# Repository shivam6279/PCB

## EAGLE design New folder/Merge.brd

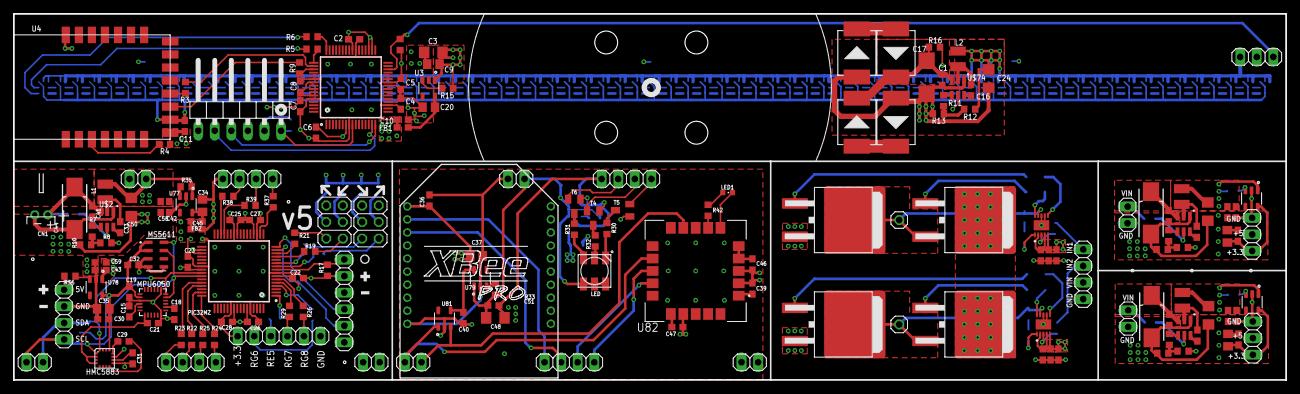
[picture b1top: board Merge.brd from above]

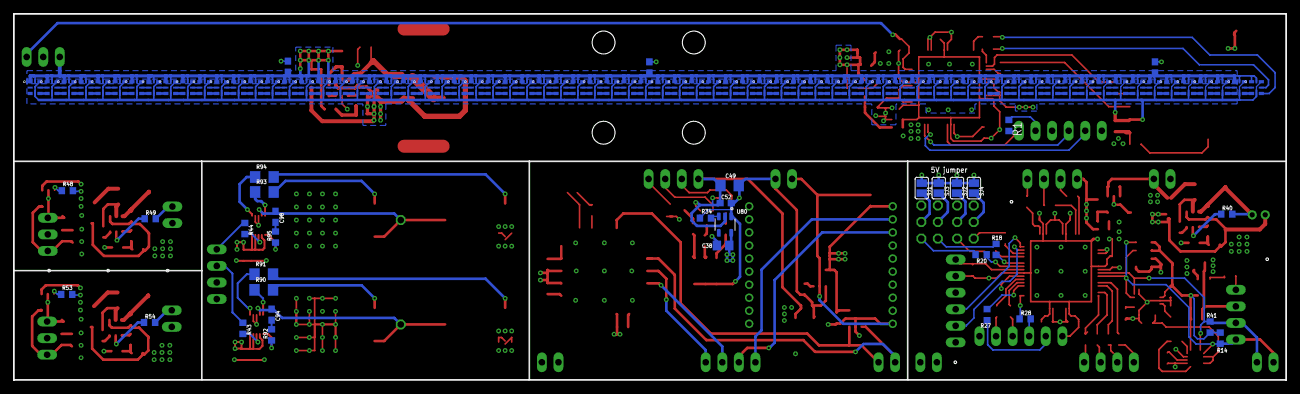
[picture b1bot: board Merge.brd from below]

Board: 4 copper layers, 195.0 x 56.1 mm, 281 parts (107 on the bottom side), 289 nets.

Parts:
C1, C2, C4, C5, C6, C7, C8, C10, C11, C12, C13, C14, C15, C16, C21, C22, C23, C25, C26, C27, C28, C30, C32, C33, C36, C39, C40, C41, C42, C43, C45, C46, C47, C51, C52, C53, C55, C56, C58, C59, C60, C62, C63, C65, C66, C68, C70: 0.1uF; C0603
C3, C24, C48, C49, C50, C61, C69: 10uF; C1206
C9: C0805
C17: C/6032-28R
C18: 2.2nF; C0603
C19: 10nF; C0603
C20, C34, C35, C37, C38, C54, C64: 1uF; C0805
C29: 0.22uF; C0603
C31: 4.7uF; C0603
C44, C57, C67: 085CS_1AR
C91, C92, C93, C94, C95, C96, C97, C98: C0603
CN1: JST-PH-2-THM-RA
D2, D3, D4, D5: SMD-DIODE-SCHOTTKY-40V-3A(DO-214AB); DO-214AB
E$1: 1X04
E$2, E$4: 1X02
E$3, E$5: 1X03
FB1, FB2: 30Ω/1.8A; 0603
HMC5883: HMC5883L; LPCC-16
JP1: 1X06/90
JP2: 1X03
JP3, JP10, JP12, JP13, JP14, JP15: 1X02
JP4, JP5: 2X03
JP6, JP7, JP8, JP9, JP11: 1X04
JP16, JP17: 1X06
JP29, JP30: 1X01
L1, L2, L3, L4: 4.7uH; L2825P
LED: RGBLED5050
LED1: CHIPLED_0603
MPU6050: MPU-6050; QFN50P400X400X95-24N
MS5611: MS561101BA03-50; SON125P500X300X100-8N
PIC32MZ: PIC32MZ2048EFH064-I/PT; QFP50P1200X1200X120-64N
R1, R2, R3, R4, R5, R6, R9, R43, R44, R92, R95: R0603
R7, R11, R15, R45, R50: 75k; R0603
R8, R12, R46, R51: 41k; R0603
R10, R13, R47, R52: 7.6k; R0603
R14, R41: 4.7k; R0603
R16: 20k; R0603
R17, R42: 1k; R0603
R18, R19, R20, R21, R22, R23, R24, R25, R26, R27, R28, R29, R37, R38, R39: 33; R0603
R30, R31: 330; R0603
R32: 220; R0603
R33, R34, R35, R36, R40, R48, R49, R53, R54: 10k; R0603
R90, R91, R93, R94: R1206
SJ1, SJ2, SJ3, SJ4: SJ
T1, T2, T3, T7: D2PAK_TO263
T4, T5, T6: SOT23-EBC
U1: PIC32MZ2048EFH064-I/PT; QFP50P1200X1200X120-64N
U2, U5, U6, U7, U8, U9, U10, U11, U12, U13, U14, U15, U16, U17, U18, U19, U20, U21, U22, U23, U24, U25, U26, U27, U28, U29, U30, U31, U32, U33, U34, U35, U36, U37, U38, U39, U40, U41, U42, U43, U44, U45, U46, U47, U48, U49, U50, U51, U52, U53, U54, U55, U56, U57, U58, U59, U60, U61, U62, U63, U64, U65, U66, U67, U68, U69, U70, U71, U72, U73, U74, U75, U76: 3341; LED_3341
U3, U77, U78, U79, U80, U83, U84: TLV75533PDBVR; SOT95P280X145-5N
U4: EMB1061
U81: CAT24C02; SOT95P280X145-5N
U82: SAM-M8Q; XCVR_SAM-M8Q
U90, U91: CHL8510CRT; 10-VFDFN
U$1, U$2, U$3, U$74: AP65211A; SOT95P280X140-6N
XB2: XBEE-PRO

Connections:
+3V1: C22.1, C23.1, C25.1, C26.1, C27.1, C28.1, C45.1, FB2.2, JP16.6, JP17.2, PIC32MZ.8, PIC32MZ.19, PIC32MZ.26, PIC32MZ.39, PIC32MZ.54, PIC32MZ.60, R17.2
+3V3: C2.1, C4.1, C5.1, C6.1, C7.1, C8.1, C10.1, C11.1, FB1.2, JP1.5, R1.1, R2.1, R4.1, U1.8, U1.19, U1.26, U1.39, U1.54, U1.60, U4.P$8
+5V: C3.1, C9.1, C12.1, C13.1, C14.1, C24.1, JP2.1, L2.1, R12.2, R15.1, U2.1, U2.8, U3.1, U5.1, U5.8, U6.1, U6.8, U7.1, U7.8, U8.1, U8.8, U9.1, U9.8, U10.1, U10.8, U11.1, U11.8, U12.1, U12.8, U13.1, U13.8, U14.1, U14.8, U15.1, U15.8, U16.1, U16.8, U17.1, U17.8, U18.1, U18.8, U19.1, U19.8, U20.1, U20.8, U21.1, U21.8, U22.1, U22.8, U23.1, U23.8, U24.1, U24.8, U25.1, U25.8, U26.1, U26.8, U27.1, U27.8, U28.1, U28.8, U29.1, U29.8, U30.1, U30.8, U31.1, U31.8, U32.1, U32.8, U33.1, U33.8, U34.1, U34.8, U35.1, U35.8, U36.1, U36.8, U37.1, U37.8, U38.1, U38.8, U39.1, U39.8, U40.1, U40.8, U41.1, U41.8, U42.1, U42.8, U43.1, U43.8, U44.1, U44.8, U45.1, U45.8, U46.1, U46.8, U47.1, U47.8, U48.1, U48.8, U49.1, U49.8, U50.1, U50.8, U51.1, U51.8, U52.1, U52.8, U53.1, U53.8, U54.1, U54.8, U55.1, U55.8, U56.1, U56.8, U57.1, U57.8, U58.1, U58.8, U59.1, U59.8, U60.1, U60.8, U61.1, U61.8, U62.1, U62.8, U63.1, U63.8, U64.1, U64.8, U65.1, U65.8, U66.1, U66.8, U67.1, U67.8, U68.1, U68.8, U69.1, U69.8, U70.1, U70.8, U71.1, U71.8, U72.1, U72.8, U73.1, U73.8, U74.1, U74.8, U75.1, U75.8, U76.1, U76.8
+5V1: C42.1, C43.1, C50.1, C58.1, C59.1, JP7.4, JP10.1, L1.1, R8.2, R35.2, R36.2, SJ1.2, SJ2.2, SJ3.2, SJ4.2, U77.1, U78.1
+5V2: C56.1, C61.1, C62.1, E$3.2, L3.1, R46.2, R48.2, U83.1
+5V3: C66.1, C69.1, C70.1, E$5.2, L4.1, R51.2, R53.2, U84.1
+5V/1: C48.1, C49.1, C51.1, C52.1, JP13.1, LED.1, LED.2, LED.3, R33.2, R34.2, U79.1, U80.1
+12V: C41.1, C44.+, CN1.1, R40.2, U$2.3
+12V1: C55.1, C57.+, E$2.2, R49.2, U$1.3
+12V2: C91.1, C92.1, C93.1, C95.1, C96.1, C97.1, E$1.2, T1.2, T3.2, U90.2, U90.4, U90.5, U91.2, U91.4, U91.5
+12V3: C65.1, C67.+, E$4.2, R54.2, U$3.3
+15V: C1.1, C17.+, D2.2, D3.2, R16.2, U$74.3
BLE_RX: R3.2, U4.P$11
BLE_TX: R9.2, U4.P$10
CKI_1: R5.2, U2.5
DGND: C36.2, C37.2, C38.2, C39.2, C40.2, C46.2, C47.2, C48.2, C49.2, C51.2, C52.2, JP8.4, JP13.2, JP14.1, JP14.2, LED1.C, T4.E, T5.E, T6.E, U79.2, U80.2, U81.2, U82.1, U82.4, U82.5, U82.6, U82.10, U82.11, U82.15, U82.16, U82.20, XB2.10
ESC_1: JP5.1, R20.2
ESC_2: JP5.2, R18.2
ESC_3: JP4.1, R19.2
ESC_4: JP4.2, R21.2
GATE_H1: R90.2, T1.1
GATE_H2: R93.2, T3.1
GATE_L1: R91.2, T7.1
GATE_L2: R94.2, T2.1
GND1: C1.2, C2.2, C3.2, C4.2, C5.2, C6.2, C7.2, C8.2, C9.2, C10.2, C11.2, C12.2, C13.2, C14.2, C15.2, C17.-, C18.2, C19.2, C20.2, C21.2, C22.2, C23.2, C24.2, C25.2, C26.2, C27.2, C28.2, C30.2, C31.2, C32.2, C34.2, C35.2, C41.2, C42.2, C43.2, C44.-, C45.2, C50.2, C58.2, C59.2, CN1.2, D4.1, D5.1, HMC5883.9, HMC5883.11, JP1.4, JP2.2, JP4.5, JP4.6, JP5.5, JP5.6, JP7.3, JP9.4, JP10.2, JP15.1, JP15.2, JP16.1, JP17.3, MPU6050.1, MPU6050.9, MPU6050.18, MS5611.3, MS5611.4, MS5611.5, PIC32MZ.7, PIC32MZ.20, PIC32MZ.25, PIC32MZ.34, PIC32MZ.35, PIC32MZ.40, PIC32MZ.55, PIC32MZ.59, R10.1, R13.1, U1.7, U1.20, U1.25, U1.34, U1.35, U1.40, U1.55, U1.59, U2.6, U2.7, U3.2, U4.P$9, U4.P$22, U5.6, U5.7, U6.6, U6.7, U7.6, U7.7, U8.6, U8.7, U9.6, U9.7, U10.6, U10.7, U11.6, U11.7, U12.6, U12.7, U13.6, U13.7, U14.6, U14.7, U15.6, U15.7, U16.6, U16.7, U17.6, U17.7, U18.6, U18.7, U19.6, U19.7, U20.6, U20.7, U21.6, U21.7, U22.6, U22.7, U23.6, U23.7, U24.6, U24.7, U25.6, U25.7, U26.6, U26.7, U27.6, U27.7, U28.6, U28.7, U29.6, U29.7, U30.6, U30.7, U31.6, U31.7, U32.6, U32.7, U33.6, U33.7, U34.6, U34.7, U35.6, U35.7, U36.6, U36.7, U37.6, U37.7, U38.6, U38.7, U39.6, U39.7, U40.6, U40.7, U41.6, U41.7, U42.6, U42.7, U43.6, U43.7, U44.6, U44.7, U45.6, U45.7, U46.6, U46.7, U47.6, U47.7, U48.6, U48.7, U49.6, U49.7, U50.6, U50.7, U51.6, U51.7, U52.6, U52.7, U53.6, U53.7, U54.6, U54.7, U55.6, U55.7, U56.6, U56.7, U57.6, U57.7, U58.6, U58.7, U59.6, U59.7, U60.6, U60.7, U61.6, U61.7, U62.6, U62.7, U63.6, U63.7, U64.6, U64.7, U65.6, U65.7, U66.6, U66.7, U67.6, U67.7, U68.6, U68.7, U69.6, U69.7, U70.6, U70.7, U71.6, U71.7, U72.6, U72.7, U73.6, U73.7, U74.6, U74.7, U75.6, U75.7, U76.6, U76.7, U77.2, U78.2, U$2.1, U$74.1
GND2: C54.2, C55.2, C56.2, C57.-, C60.1, C61.2, C62.2, E$2.1, E$3.1, R47.1, U83.2, U$1.1
GND3: C91.2, C92.2, C93.2, C95.2, C96.2, C97.2, E$1.1, T2.3, T7.3, U90.7, U90.8, U90.11, U91.7, U91.8, U91.11
GND4: C64.2, C65.2, C66.2, C67.-, C68.1, C69.2, C70.2, E$4.1, E$5.1, R52.1, U84.2, U$3.1
GPIO1: JP16.5, R27.2
GPIO2: JP16.4, R28.2
GPIO3: JP16.3, R29.2
GPIO4: JP16.2, R26.2
GPS_RX: JP11.1, R23.1
GPS_RX_J: JP6.3, U82.14
GPS_TX: JP11.2, R22.1
GPS_TX_J: JP6.4, U82.13
H_OUT1: C94.1, JP29.1, T1.3, T7.2, U90.9
H_OUT2: C98.1, JP30.1, T2.2, T3.3, U91.9
LED_BLUE: JP9.1, R37.2
LED_BLUE1: JP8.1, T5.B
LED_GREEN: JP9.3, R38.2
LED_GREEN1: JP8.2, T4.B
LED_RED: JP9.2, R39.2
MCLR: JP17.1, PIC32MZ.9, R17.1
unnamed: D2.1, D5.2
unnamed: D3.1, D4.2
unnamed: R15.2, U3.3
unnamed: R9.1, U1.51
unnamed: R4.2, U4.P$3
unnamed: R16.1, U$74.5
unnamed: U5.2, U6.5
unnamed: U5.3, U6.4
unnamed: U2.2, U5.5
unnamed: U2.3, U5.4
unnamed: U6.2, U7.5
unnamed: JP1.3, U1.16
unnamed: JP1.2, U1.15
unnamed: JP1.6, R1.2, U1.9
unnamed: U26.2, U27.5
unnamed: U6.3, U7.4
unnamed: U7.2, U8.5
unnamed: U7.3, U8.4
unnamed: R3.1, U1.50
unnamed: U8.2, U9.5
unnamed: R6.1, U1.48
unnamed: U8.3, U9.4
unnamed: U9.2, U10.5
unnamed: U9.3, U10.4
unnamed: U10.2, U11.5
unnamed: U10.3, U11.4
unnamed: U11.2, U12.5
unnamed: U11.3, U12.4
unnamed: U12.2, U13.5
unnamed: U12.3, U13.4
unnamed: U13.2, U14.5
unnamed: U13.3, U14.4
unnamed: U14.2, U15.5
unnamed: U14.3, U15.4
unnamed: U15.2, U17.5
unnamed: U15.3, U17.4
unnamed: U16.5, U17.2
unnamed: U16.4, U17.3
unnamed: U18.2, U19.5
unnamed: U18.3, U19.4
unnamed: U16.2, U18.5
unnamed: R5.1, U1.49
unnamed: U16.3, U18.4
unnamed: U19.2, U20.5
unnamed: U19.3, U20.4
unnamed: U20.2, U21.5
unnamed: JP2.3, R2.2, U1.30
unnamed: U20.3, U21.4
unnamed: U21.2, U22.5
unnamed: U21.3, U22.4
unnamed: U22.2, U23.5
unnamed: U22.3, U23.4
unnamed: U23.2, U24.5
unnamed: U23.3, U24.4
unnamed: U24.2, U25.5
unnamed: U24.3, U25.4
unnamed: U25.2, U26.5
unnamed: U25.3, U26.4
unnamed: C20.1, FB1.1, U3.5
unnamed: U26.3, U27.4
unnamed: U27.2, U28.5
unnamed: U27.3, U28.4
unnamed: U28.2, U30.5
unnamed: U28.3, U30.4
unnamed: U29.5, U30.2
unnamed: U29.4, U30.3
unnamed: U31.2, U32.5
unnamed: U31.3, U32.4
unnamed: U29.2, U31.5
unnamed: U29.3, U31.4
unnamed: U32.2, U33.5
unnamed: U32.3, U33.4
unnamed: U33.2, U34.5
unnamed: U33.3, U34.4
unnamed: U34.2, U35.5
unnamed: U34.3, U35.4
unnamed: U35.2, U36.5
unnamed: U35.3, U36.4
unnamed: U36.2, U37.5
unnamed: U36.3, U37.4
unnamed: U37.2, U38.5
unnamed: U37.3, U38.4
unnamed: U38.2, U39.5
unnamed: U38.3, U39.4
unnamed: U39.2, U40.5
unnamed: U39.3, U40.4
unnamed: U40.2, U41.5
unnamed: U40.3, U41.4
unnamed: U41.2, U43.5
unnamed: U41.3, U43.4
unnamed: U42.5, U43.2
unnamed: U42.4, U43.3
unnamed: U44.2, U45.5
unnamed: U44.3, U45.4
unnamed: U42.2, U44.5
unnamed: U42.3, U44.4
unnamed: U45.2, U46.5
unnamed: U45.3, U46.4
unnamed: U46.2, U47.5
unnamed: U46.3, U47.4
unnamed: U47.2, U48.5
unnamed: U47.3, U48.4
unnamed: U48.2, U49.5
unnamed: U48.3, U49.4
unnamed: U49.2, U50.5
unnamed: U49.3, U50.4
unnamed: U50.2, U51.5
unnamed: C15.1, MPU6050.10
unnamed: U50.3, U51.4
unnamed: U51.2, U52.5
unnamed: U51.3, U52.4
unnamed: U52.2, U53.5
unnamed: U52.3, U53.4
unnamed: U53.2, U54.5
unnamed: U53.3, U54.4
unnamed: U54.2, U56.5
unnamed: U54.3, U56.4
unnamed: U55.5, U56.2
unnamed: U55.4, U56.3
unnamed: U57.2, U58.5
unnamed: U57.3, U58.4
unnamed: U55.2, U57.5
unnamed: U55.3, U57.4
unnamed: U58.2, U59.5
unnamed: C16.1, L2.2, U$74.2
unnamed: C16.2, U$74.6
unnamed: U58.3, U59.4
unnamed: U59.2, U60.5
unnamed: U59.3, U60.4
unnamed: U60.2, U61.5
unnamed: U60.3, U61.4
unnamed: U61.2, U62.5
unnamed: U61.3, U62.4
unnamed: U62.2, U63.5
unnamed: U62.3, U63.4
unnamed: U63.2, U64.5
unnamed: U63.3, U64.4
unnamed: U64.2, U65.5
unnamed: U64.3, U65.4
unnamed: U65.2, U66.5
unnamed: U65.3, U66.4
unnamed: U66.2, U67.5
unnamed: U66.3, U67.4
unnamed: U67.2, U69.5
unnamed: U67.3, U69.4
unnamed: U68.5, U69.2
unnamed: U68.4, U69.3
unnamed: U70.2, U71.5
unnamed: U70.3, U71.4
unnamed: U68.2, U70.5
unnamed: U68.3, U70.4
unnamed: U71.2, U72.5
unnamed: U71.3, U72.4
unnamed: U72.2, U73.5
unnamed: U72.3, U73.4
unnamed: U73.2, U74.5
unnamed: U73.3, U74.4
unnamed: U74.2, U75.5
unnamed: U74.3, U75.4
unnamed: U75.2, U76.5
unnamed: U75.3, U76.4
unnamed: C18.1, MPU6050.20
unnamed: R11.1, U$74.4
unnamed: R11.2, R12.1, R13.2
unnamed: C29.1, HMC5883.8
unnamed: C29.2, HMC5883.12
unnamed: C31.1, HMC5883.10
unnamed: C33.1, L1.2, U$2.2
unnamed: C33.2, U$2.6
unnamed: R7.1, U$2.4
unnamed: R7.2, R8.1, R10.2
unnamed: PIC32MZ.11, R18.1
unnamed: PIC32MZ.13, R19.1
unnamed: PIC32MZ.10, R20.1
unnamed: PIC32MZ.14, R21.1
unnamed: PIC32MZ.45, R22.2
unnamed: PIC32MZ.44, R23.2
unnamed: PIC32MZ.48, R24.2
unnamed: PIC32MZ.47, R25.2
unnamed: PIC32MZ.5, R29.1
unnamed: PIC32MZ.6, R26.1
unnamed: R31.1, T6.C
unnamed: R32.1, T4.C
unnamed: R30.1, T5.C
unnamed: LED.5, R32.2
unnamed: LED.6, R31.2
unnamed: LED.4, R30.2
unnamed: PIC32MZ.4, R27.1
unnamed: PIC32MZ.1, R28.1
unnamed: R33.1, U79.3
unnamed: R34.1, U80.3
unnamed: R36.1, U78.3
unnamed: R35.1, U77.3
unnamed: PIC32MZ.18, R37.1
unnamed: PIC32MZ.29, R39.1
unnamed: PIC32MZ.30, R38.1
unnamed: JP8.3, T6.B
unnamed: R40.1, U$2.5
unnamed: C34.1, FB2.1, U77.5
unnamed: R42.2, U82.7
unnamed: LED1.A, R42.1
unnamed: JP4.4, SJ4.1
unnamed: JP4.3, SJ2.1
unnamed: JP5.3, SJ1.1
unnamed: JP5.4, SJ3.1
unnamed: C53.1, L3.2, U$1.2
unnamed: C53.2, U$1.6
unnamed: R45.1, U$1.4
unnamed: R45.2, R46.1, R47.2
unnamed: R48.1, U83.3
unnamed: R49.1, U$1.5
unnamed: C54.1, C60.2, E$3.3, U83.5
unnamed: C63.1, L4.2, U$3.2
unnamed: C63.2, U$3.6
unnamed: R50.1, U$3.4
unnamed: R50.2, R51.1, R52.2
unnamed: R53.1, U84.3
unnamed: R54.1, U$3.5
unnamed: C64.1, C68.2, E$5.3, U84.5
unnamed: R91.1, U90.6
unnamed: R90.1, U90.10
unnamed: C94.2, R92.2
unnamed: R92.1, U90.1
unnamed: R94.1, U91.6
unnamed: R93.1, U91.10
unnamed: C98.2, R95.2
unnamed: R95.1, U91.1
PGC: JP17.5, PIC32MZ.15
PGD: JP17.4, PIC32MZ.16
S$1: R44.2, U91.3
S$2: R43.2, U90.3
S$3: E$1.3, R43.1
S$4: E$1.4, R44.1
SCL: HMC5883.1, JP3.2, JP7.1, MPU6050.23, MS5611.8, PIC32MZ.42, R14.1
SCL_J: JP12.2, U81.1, U82.12
SDA: HMC5883.16, JP3.1, JP7.2, MPU6050.24, MS5611.7, PIC32MZ.41, R41.1
SDA_J: JP12.1, U81.3, U82.9
SDI_1: R6.2, U2.4
V+: C36.1, C37.1, C40.1, U79.5, U81.4, XB2.1
VCC: C19.1, C21.1, C30.1, C32.1, C35.1, HMC5883.2, HMC5883.4, HMC5883.13, MPU6050.8, MPU6050.13, MS5611.1, MS5611.2, R14.2, R41.2, U78.5
VDD: C38.1, C39.1, C46.1, C47.1, U80.5, U82.2, U82.3, U82.17
XBEE_RX: JP11.3, R25.1
XBEE_RX_J: JP6.2, XB2.3
XBEE_TX: JP11.4, R24.1
XBEE_TX_J: JP6.1, XB2.2

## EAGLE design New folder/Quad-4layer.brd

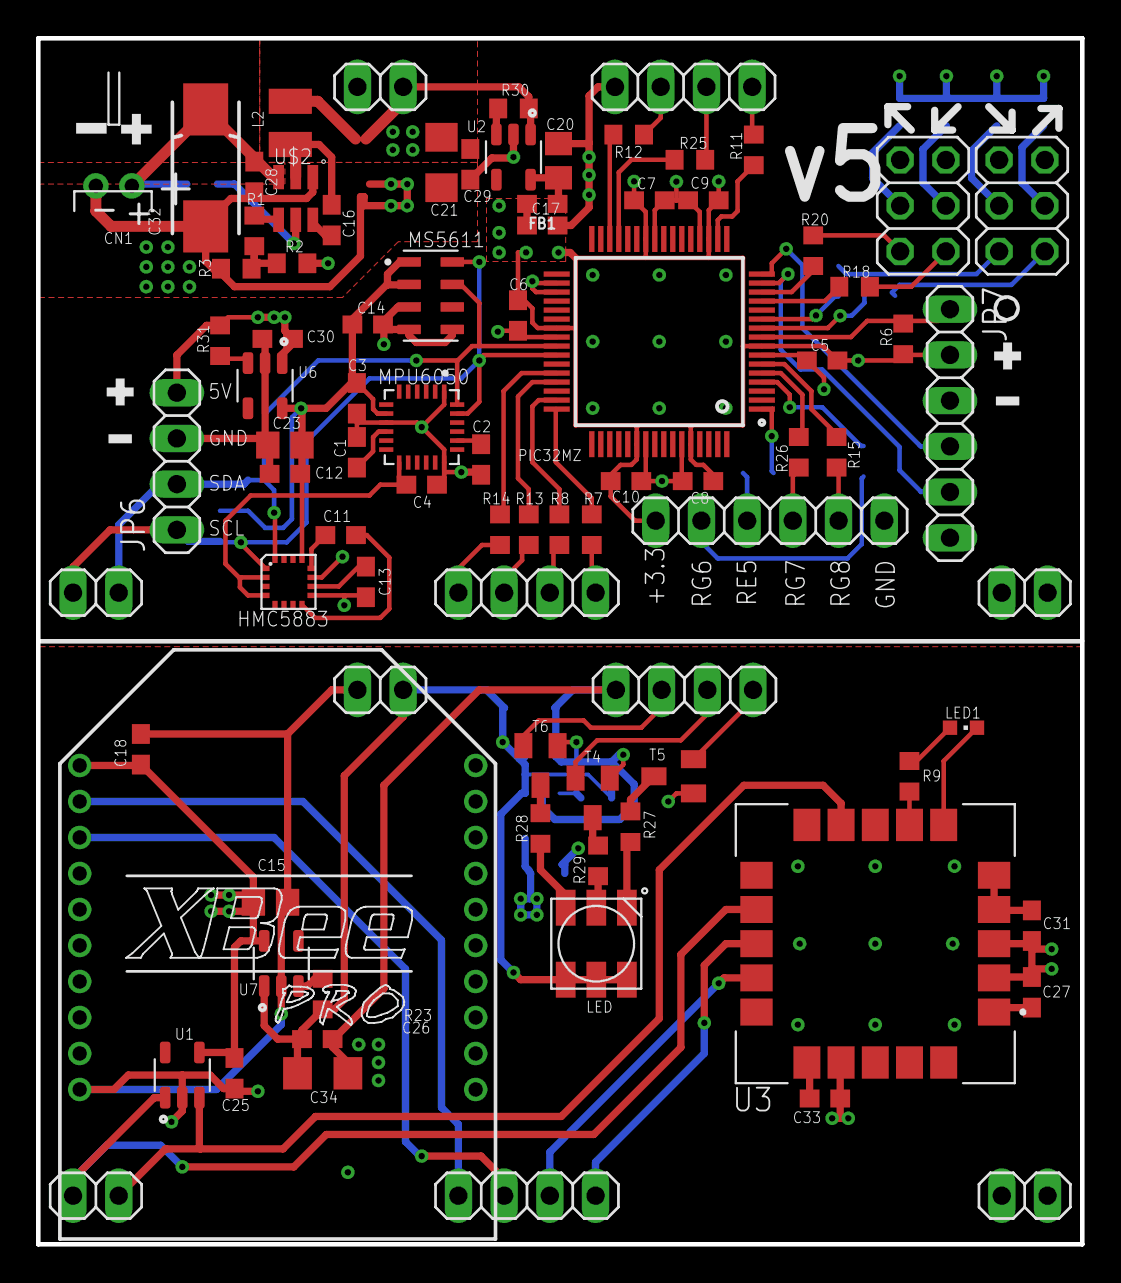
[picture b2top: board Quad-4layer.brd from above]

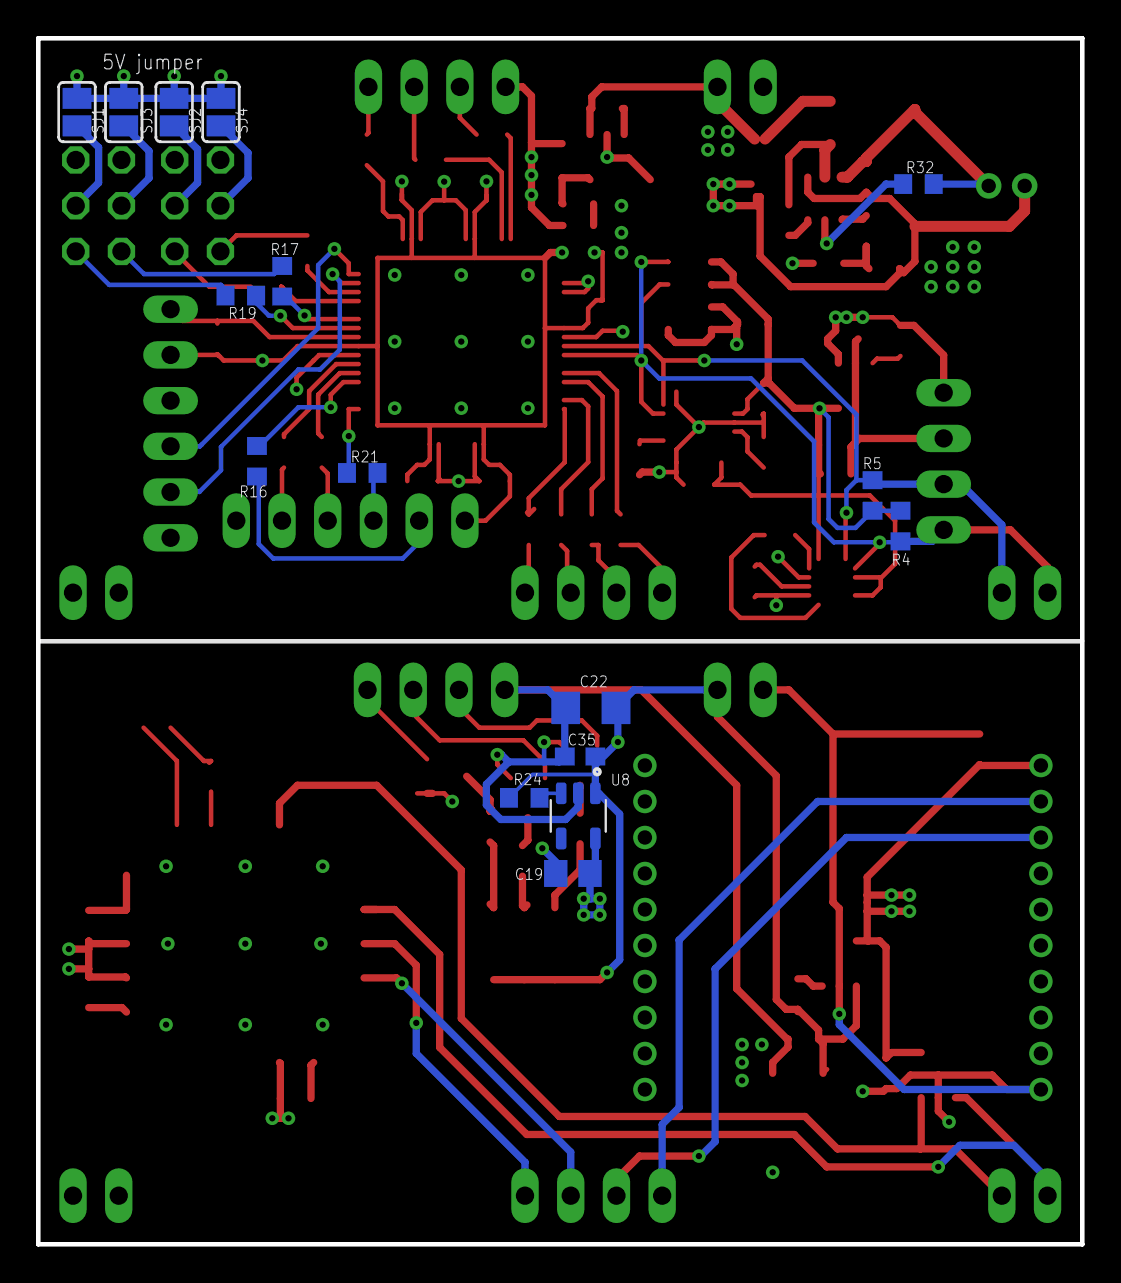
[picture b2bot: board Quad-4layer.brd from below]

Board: 4 copper layers, 58.0 x 67.0 mm, 103 parts (16 on the bottom side), 80 nets.

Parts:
C1, C4, C5, C6, C7, C8, C9, C10, C12, C14, C16, C17, C18, C25, C26, C27, C28, C29, C30, C31, C33, C35: 0.1uF; C0603
C2: 2.2nF; C0603
C3: 10nF; C0603
C11: 0.22uF; C0603
C13: 4.7uF; C0603
C15, C19, C20, C23: 1uF; C0805
C21, C22, C34: 10uF; C1206
C32: 085CS_1AR
CN1: JST-PH-2-THM-RA
FB1: 30Ω/1.8A; 0603
HMC5883: HMC5883L; LPCC-16
JP1, JP6, JP8, JP9, JP11: 1X04
JP2, JP10, JP12, JP13, JP14, JP15: 1X02
JP4, JP5: 2X03
JP7, JP16: 1X06
L2: 4.7uH; L2825P
LED: RGBLED5050
LED1: CHIPLED_0603
MPU6050: MPU-6050; QFN50P400X400X95-24N
MS5611: MS561101BA03-50; SON125P500X300X100-8N
PIC32MZ: PIC32MZ2048EFH064-I/PT; QFP50P1200X1200X120-64N
R1: 75k; R0603
R2: 41k; R0603
R3: 7.6k; R0603
R4, R5: 4.7k; R0603
R6, R9: 1k; R0603
R7, R8, R11, R12, R13, R14, R15, R16, R17, R18, R19, R20, R21, R25, R26: 33; R0603
R23, R24, R30, R31, R32: 10k; R0603
R27, R28: 330; R0603
R29: 220; R0603
SJ1, SJ2, SJ3, SJ4: SJ
T4, T5, T6: SOT23-EBC
U1: CAT24C02; SOT95P280X145-5N
U2, U6, U7, U8: TLV75533PDBVR; SOT95P280X145-5N
U3: SAM-M8Q; XCVR_SAM-M8Q
U$2: AP65211A; SOT95P280X140-6N
XB2: XBEE-PRO

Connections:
+3V3: C5.1, C6.1, C7.1, C8.1, C9.1, C10.1, C17.1, FB1.2, JP7.2, JP16.6, PIC32MZ.8, PIC32MZ.19, PIC32MZ.26, PIC32MZ.39, PIC32MZ.54, PIC32MZ.60, R6.2
+5V: C21.1, C29.1, C30.1, JP6.4, JP10.1, L2.1, R2.2, R30.2, R31.2, SJ1.2, SJ2.2, SJ3.2, SJ4.2, U2.1, U6.1
+5V/1: C22.1, C26.1, C34.1, C35.1, JP13.1, LED.1, LED.2, LED.3, R23.2, R24.2, U7.1, U8.1
+12V: C28.1, C32.+, CN1.1, R32.2, U$2.3
DGND: C15.2, C18.2, C19.2, C22.2, C25.2, C26.2, C27.2, C31.2, C33.2, C34.2, C35.2, JP8.4, JP13.2, JP14.1, JP14.2, LED1.C, T4.E, T5.E, T6.E, U1.2, U3.1, U3.4, U3.5, U3.6, U3.10, U3.11, U3.15, U3.16, U3.20, U7.2, U8.2, XB2.10
ESC_1: JP5.1, R19.2
ESC_2: JP5.2, R17.2
ESC_3: JP4.1, R18.2
ESC_4: JP4.2, R20.2
GND: C1.2, C2.2, C3.2, C4.2, C5.2, C6.2, C7.2, C8.2, C9.2, C10.2, C12.2, C13.2, C14.2, C17.2, C20.2, C21.2, C23.2, C28.2, C29.2, C30.2, C32.-, CN1.2, HMC5883.9, HMC5883.11, JP4.5, JP4.6, JP5.5, JP5.6, JP6.3, JP7.3, JP9.4, JP10.2, JP15.1, JP15.2, JP16.1, MPU6050.1, MPU6050.9, MPU6050.18, MS5611.3, MS5611.4, MS5611.5, PIC32MZ.7, PIC32MZ.20, PIC32MZ.25, PIC32MZ.34, PIC32MZ.35, PIC32MZ.40, PIC32MZ.55, PIC32MZ.59, R3.1, U2.2, U6.2, U$2.1
GPIO1: JP16.5, R16.2
GPIO2: JP16.4, R21.2
GPIO3: JP16.3, R26.2
GPIO4: JP16.2, R15.2
GPS_RX: JP11.1, R14.1
GPS_RX_J: JP1.3, U3.14
GPS_TX: JP11.2, R13.1
GPS_TX_J: JP1.4, U3.13
LED_BLUE: JP9.1, R11.2
LED_BLUE1: JP8.1, T5.B
LED_GREEN: JP9.3, R12.2
LED_GREEN1: JP8.2, T4.B
LED_RED: JP9.2, R25.2
MCLR: JP7.1, PIC32MZ.9, R6.1
unnamed: C1.1, MPU6050.10
unnamed: C2.1, MPU6050.20
unnamed: C11.1, HMC5883.8
unnamed: C11.2, HMC5883.12
unnamed: LED.5, R29.2
unnamed: C13.1, HMC5883.10
unnamed: LED.6, R28.2
unnamed: C16.1, L2.2, U$2.2
unnamed: C16.2, U$2.6
unnamed: R1.1, U$2.4
unnamed: R1.2, R2.1, R3.2
unnamed: PIC32MZ.48, R7.2
unnamed: PIC32MZ.47, R8.2
unnamed: R9.2, U3.7
unnamed: LED.4, R27.2
unnamed: LED1.A, R9.1
unnamed: PIC32MZ.18, R11.1
unnamed: PIC32MZ.45, R13.2
unnamed: PIC32MZ.44, R14.2
unnamed: PIC32MZ.29, R25.1
unnamed: PIC32MZ.4, R16.1
unnamed: PIC32MZ.1, R21.1
unnamed: PIC32MZ.11, R17.1
unnamed: PIC32MZ.13, R18.1
unnamed: PIC32MZ.10, R19.1
unnamed: PIC32MZ.14, R20.1
unnamed: R23.1, U7.3
unnamed: R24.1, U8.3
unnamed: JP4.4, SJ4.1
unnamed: PIC32MZ.5, R26.1
unnamed: PIC32MZ.6, R15.1
unnamed: R31.1, U6.3
unnamed: R30.1, U2.3
unnamed: PIC32MZ.30, R12.1
unnamed: JP8.3, T6.B
unnamed: R32.1, U$2.5
unnamed: C20.1, FB1.1, U2.5
unnamed: JP5.3, SJ1.1
unnamed: JP4.3, SJ2.1
unnamed: R28.1, T6.C
unnamed: R29.1, T4.C
unnamed: R27.1, T5.C
unnamed: JP5.4, SJ3.1
PGC: JP7.5, PIC32MZ.15
PGD: JP7.4, PIC32MZ.16
SCL: HMC5883.1, JP2.2, JP6.1, MPU6050.23, MS5611.8, PIC32MZ.42, R4.1
SCL_J: JP12.2, U1.1, U3.12
SDA: HMC5883.16, JP2.1, JP6.2, MPU6050.24, MS5611.7, PIC32MZ.41, R5.1
SDA_J: JP12.1, U1.3, U3.9
V+: C15.1, C18.1, C25.1, U1.4, U7.5, XB2.1
VCC: C3.1, C4.1, C12.1, C14.1, C23.1, HMC5883.2, HMC5883.4, HMC5883.13, MPU6050.8, MPU6050.13, MS5611.1, MS5611.2, R4.2, R5.2, U6.5
VDD: C19.1, C27.1, C31.1, C33.1, U3.2, U3.3, U3.17, U8.5
XBEE_RX: JP11.3, R8.1
XBEE_RX_J: JP1.2, XB2.3
XBEE_TX: JP11.4, R7.1
XBEE_TX_J: JP1.1, XB2.2

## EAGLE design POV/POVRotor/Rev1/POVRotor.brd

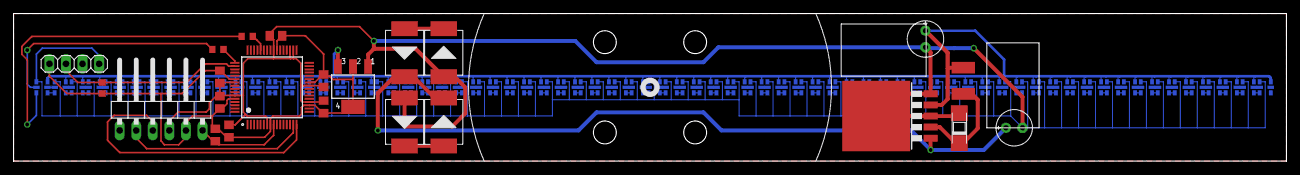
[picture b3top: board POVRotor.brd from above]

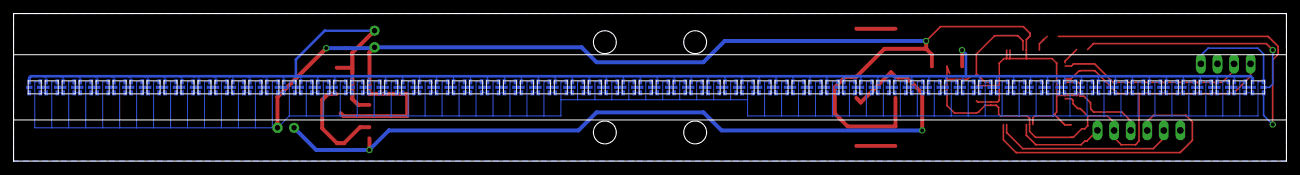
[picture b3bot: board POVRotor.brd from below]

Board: 2 copper layers, 195.0 x 22.6 mm, 96 parts (73 on the bottom side), 159 nets.

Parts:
C1, C3: E2,5-6E
C2, C4, C5, C6, C7, C8: C0805
D1: SOD106A
D2, D3, D4, D5: SMD-DIODE-SCHOTTKY-40V-3A(DO-214AB); DO-214AB
IC1: LM2576S; TO263-5
IC2: SOT223
JP1: 1X06/90
JP2: 1X04
L2: L4532P
R1: R0805
R2, R4, R5: R0603
U1: PIC32MZ2048EFH064-I/PT; QFP50P1200X1200X120-64N
U$1, U$2, U$3, U$4, U$5, U$6, U$7, U$8, U$9, U$10, U$11, U$12, U$13, U$14, U$15, U$16, U$17, U$18, U$19, U$20, U$21, U$22, U$23, U$24, U$25, U$26, U$27, U$28, U$29, U$30, U$31, U$32, U$33, U$34, U$35, U$36, U$37, U$38, U$39, U$40, U$41, U$42, U$43, U$44, U$45, U$46, U$47, U$48, U$49, U$50, U$51, U$52, U$53, U$54, U$55, U$56, U$57, U$58, U$59, U$60, U$61, U$62, U$63, U$64, U$65, U$66, U$67, U$68, U$69, U$70, U$71, U$72, U$73: 2020LED

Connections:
+3V3: C2.1, C4.1, C5.1, C6.1, C7.1, C8.1, IC2.2, JP1.5, JP2.1, R1.1, R2.1, U1.8, U1.19, U1.26, U1.39, U1.54, U1.60
+5V: C1.+, IC1.4, IC2.3, L2.2, U$1.VCC, U$2.VCC, U$3.VCC, U$4.VCC, U$5.VCC, U$6.VCC, U$7.VCC, U$8.VCC, U$9.VCC, U$10.VCC, U$11.VCC, U$12.VCC, U$13.VCC, U$14.VCC, U$15.VCC, U$16.VCC, U$17.VCC, U$18.VCC, U$19.VCC, U$20.VCC, U$21.VCC, U$22.VCC, U$23.VCC, U$24.VCC, U$25.VCC, U$26.VCC, U$27.VCC, U$28.VCC, U$29.VCC, U$30.VCC, U$31.VCC, U$32.VCC, U$33.VCC, U$34.VCC, U$35.VCC, U$36.VCC, U$37.VCC, U$38.VCC, U$39.VCC, U$40.VCC, U$41.VCC, U$42.VCC, U$43.VCC, U$44.VCC, U$45.VCC, U$46.VCC, U$47.VCC, U$48.VCC, U$49.VCC, U$50.VCC, U$51.VCC, U$52.VCC, U$53.VCC, U$54.VCC, U$55.VCC, U$56.VCC, U$57.VCC, U$58.VCC, U$59.VCC, U$60.VCC, U$61.VCC, U$62.VCC, U$63.VCC, U$64.VCC, U$65.VCC, U$66.VCC, U$67.VCC, U$68.VCC, U$69.VCC, U$70.VCC, U$71.VCC, U$72.VCC, U$73.VCC
+15V: C3.+, D2.2, D3.2, IC1.1
GND: C1.-, C2.2, C3.-, C4.2, C5.2, C6.2, C7.2, C8.2, D1.A, D4.1, D5.1, IC1.3, IC1.5, IC2.1, JP1.4, JP2.4, U1.7, U1.20, U1.25, U1.34, U1.35, U1.40, U1.55, U1.59, U$1.GND, U$2.GND, U$3.GND, U$4.GND, U$5.GND, U$6.GND, U$7.GND, U$8.GND, U$9.GND, U$10.GND, U$11.GND, U$12.GND, U$13.GND, U$14.GND, U$15.GND, U$16.GND, U$17.GND, U$18.GND, U$19.GND, U$20.GND, U$21.GND, U$22.GND, U$23.GND, U$24.GND, U$25.GND, U$26.GND, U$27.GND, U$28.GND, U$29.GND, U$30.GND, U$31.GND, U$32.GND, U$33.GND, U$34.GND, U$35.GND, U$36.GND, U$37.GND, U$38.GND, U$39.GND, U$40.GND, U$41.GND, U$42.GND, U$43.GND, U$44.GND, U$45.GND, U$46.GND, U$47.GND, U$48.GND, U$49.GND, U$50.GND, U$51.GND, U$52.GND, U$53.GND, U$54.GND, U$55.GND, U$56.GND, U$57.GND, U$58.GND, U$59.GND, U$60.GND, U$61.GND, U$62.GND, U$63.GND, U$64.GND, U$65.GND, U$66.GND, U$67.GND, U$68.GND, U$69.GND, U$70.GND, U$71.GND, U$72.GND, U$73.GND
unnamed: D2.1, D5.2
unnamed: D3.1, D4.2
unnamed: D1.K, IC1.2, L2.1
unnamed: JP2.2, R2.2, U1.50
unnamed: U$1.SDI, U$2.SDO
unnamed: U$10.SDO, U$11.SDI
unnamed: U$10.CLKO, U$11.CLKI
unnamed: U$1.CLKI, U$2.CLKO
unnamed: U$11.SDO, U$12.SDI
unnamed: JP1.3, U1.16
unnamed: JP1.2, U1.15
unnamed: JP1.6, R1.2, U1.9
unnamed: R4.2, U$2.SDI
unnamed: U$1.SDO, U$3.SDI
unnamed: R5.2, U$2.CLKI
unnamed: R5.1, U1.49
unnamed: U$1.CLKO, U$3.CLKI
unnamed: R4.1, U1.44
unnamed: U$11.CLKO, U$12.CLKI
unnamed: U$12.SDO, U$13.SDI
unnamed: U$12.CLKO, U$13.CLKI
unnamed: U$13.SDO, U$14.SDI
unnamed: U$3.SDO, U$4.SDI
unnamed: U$3.CLKO, U$4.CLKI
unnamed: U$13.CLKO, U$14.CLKI
unnamed: U$14.SDO, U$15.SDI
unnamed: U$14.CLKO, U$15.CLKI
unnamed: U$4.SDO, U$5.SDI
unnamed: U$4.CLKO, U$5.CLKI
unnamed: U$15.SDO, U$16.SDI
unnamed: U$15.CLKO, U$16.CLKI
unnamed: U$16.SDO, U$17.SDI
unnamed: U$16.CLKO, U$17.CLKI
unnamed: U$5.SDO, U$6.SDI
unnamed: U$5.CLKO, U$6.CLKI
unnamed: U$17.SDO, U$18.SDI
unnamed: U$17.CLKO, U$18.CLKI
unnamed: U$18.SDO, U$19.SDI
unnamed: U$18.CLKO, U$19.CLKI
unnamed: U$6.SDO, U$7.SDI
unnamed: U$19.SDO, U$20.SDI
unnamed: U$19.CLKO, U$20.CLKI
unnamed: U$20.SDO, U$21.SDI
unnamed: U$20.CLKO, U$21.CLKI
unnamed: U$21.SDO, U$22.SDI
unnamed: U$6.CLKO, U$7.CLKI
unnamed: U$21.CLKO, U$22.CLKI
unnamed: U$22.SDO, U$23.SDI
unnamed: U$22.CLKO, U$23.CLKI
unnamed: U$23.SDO, U$24.SDI
unnamed: U$23.CLKO, U$24.CLKI
unnamed: U$7.SDO, U$8.SDI
unnamed: U$24.SDO, U$25.SDI
unnamed: U$7.CLKO, U$8.CLKI
unnamed: U$24.CLKO, U$25.CLKI
unnamed: U$25.SDO, U$26.SDI
unnamed: U$25.CLKO, U$26.CLKI
unnamed: U$8.SDO, U$9.SDI
unnamed: U$8.CLKO, U$9.CLKI
unnamed: U$26.SDO, U$27.SDI
unnamed: U$26.CLKO, U$27.CLKI
unnamed: U$9.SDO, U$10.SDI
unnamed: U$9.CLKO, U$10.CLKI
unnamed: U$27.SDO, U$28.SDI
unnamed: U$27.CLKO, U$28.CLKI
unnamed: U$28.SDO, U$29.SDI
unnamed: U$28.CLKO, U$29.CLKI
unnamed: U$29.SDO, U$30.SDI
unnamed: U$29.CLKO, U$30.CLKI
unnamed: U$30.SDO, U$31.SDI
unnamed: U$30.CLKO, U$31.CLKI
unnamed: U$31.SDO, U$32.SDI
unnamed: U$31.CLKO, U$32.CLKI
unnamed: U$32.SDO, U$33.SDI
unnamed: U$32.CLKO, U$33.CLKI
unnamed: U$33.SDO, U$34.SDI
unnamed: U$33.CLKO, U$34.CLKI
unnamed: U$34.SDO, U$35.SDI
unnamed: U$34.CLKO, U$35.CLKI
unnamed: U$35.SDO, U$36.SDI
unnamed: U$35.CLKO, U$36.CLKI
unnamed: U$36.SDO, U$37.SDI
unnamed: U$36.CLKO, U$37.CLKI
unnamed: U$37.SDO, U$38.SDI
unnamed: U$37.CLKO, U$38.CLKI
unnamed: U$38.SDO, U$39.SDI
unnamed: U$38.CLKO, U$39.CLKI
unnamed: U$39.SDO, U$40.SDI
unnamed: U$39.CLKO, U$40.CLKI
unnamed: U$40.SDO, U$41.SDI
unnamed: U$40.CLKO, U$41.CLKI
unnamed: U$41.SDO, U$42.SDI
unnamed: U$41.CLKO, U$42.CLKI
unnamed: U$42.SDO, U$43.SDI
unnamed: U$42.CLKO, U$43.CLKI
unnamed: U$43.SDO, U$44.SDI
unnamed: U$43.CLKO, U$44.CLKI
unnamed: U$44.SDO, U$45.SDI
unnamed: U$44.CLKO, U$45.CLKI
unnamed: U$45.SDO, U$46.SDI
unnamed: U$45.CLKO, U$46.CLKI
unnamed: U$46.SDO, U$47.SDI
unnamed: U$46.CLKO, U$47.CLKI
unnamed: U$47.SDO, U$48.SDI
unnamed: U$47.CLKO, U$48.CLKI
unnamed: U$48.SDO, U$49.SDI
unnamed: U$48.CLKO, U$49.CLKI
unnamed: U$49.SDO, U$50.SDI
unnamed: U$49.CLKO, U$50.CLKI
unnamed: U$50.SDO, U$51.SDI
unnamed: U$50.CLKO, U$51.CLKI
unnamed: U$51.SDO, U$52.SDI
unnamed: U$51.CLKO, U$52.CLKI
unnamed: U$52.SDO, U$53.SDI
unnamed: U$52.CLKO, U$53.CLKI
unnamed: U$53.SDO, U$54.SDI
unnamed: U$53.CLKO, U$54.CLKI
unnamed: U$54.SDO, U$55.SDI
unnamed: U$54.CLKO, U$55.CLKI
unnamed: U$55.SDO, U$56.SDI
unnamed: U$55.CLKO, U$56.CLKI
unnamed: U$56.SDO, U$57.SDI
unnamed: U$56.CLKO, U$57.CLKI
unnamed: U$57.SDO, U$58.SDI
unnamed: U$57.CLKO, U$58.CLKI
unnamed: U$58.SDO, U$59.SDI
unnamed: U$58.CLKO, U$59.CLKI
unnamed: U$59.SDO, U$60.SDI
unnamed: U$59.CLKO, U$60.CLKI
unnamed: U$60.SDO, U$61.SDI
unnamed: U$60.CLKO, U$61.CLKI
unnamed: U$61.SDO, U$62.SDI
unnamed: U$61.CLKO, U$62.CLKI
unnamed: U$62.SDO, U$63.SDI
unnamed: U$62.CLKO, U$63.CLKI
unnamed: U$63.SDO, U$64.SDI
unnamed: U$63.CLKO, U$64.CLKI
unnamed: U$64.SDO, U$65.SDI
unnamed: U$64.CLKO, U$65.CLKI
unnamed: U$65.SDO, U$66.SDI
unnamed: U$65.CLKO, U$66.CLKI
unnamed: U$66.SDO, U$67.SDI
unnamed: U$66.CLKO, U$67.CLKI
unnamed: U$67.SDO, U$68.SDI
unnamed: U$67.CLKO, U$68.CLKI
unnamed: U$68.SDO, U$69.SDI
unnamed: U$68.CLKO, U$69.CLKI
unnamed: U$69.SDO, U$70.SDI
unnamed: U$69.CLKO, U$70.CLKI
unnamed: U$70.SDO, U$71.SDI
unnamed: U$70.CLKO, U$71.CLKI
unnamed: U$71.SDO, U$72.SDI
unnamed: U$71.CLKO, U$72.CLKI
unnamed: U$72.SDO, U$73.SDI
unnamed: U$72.CLKO, U$73.CLKI

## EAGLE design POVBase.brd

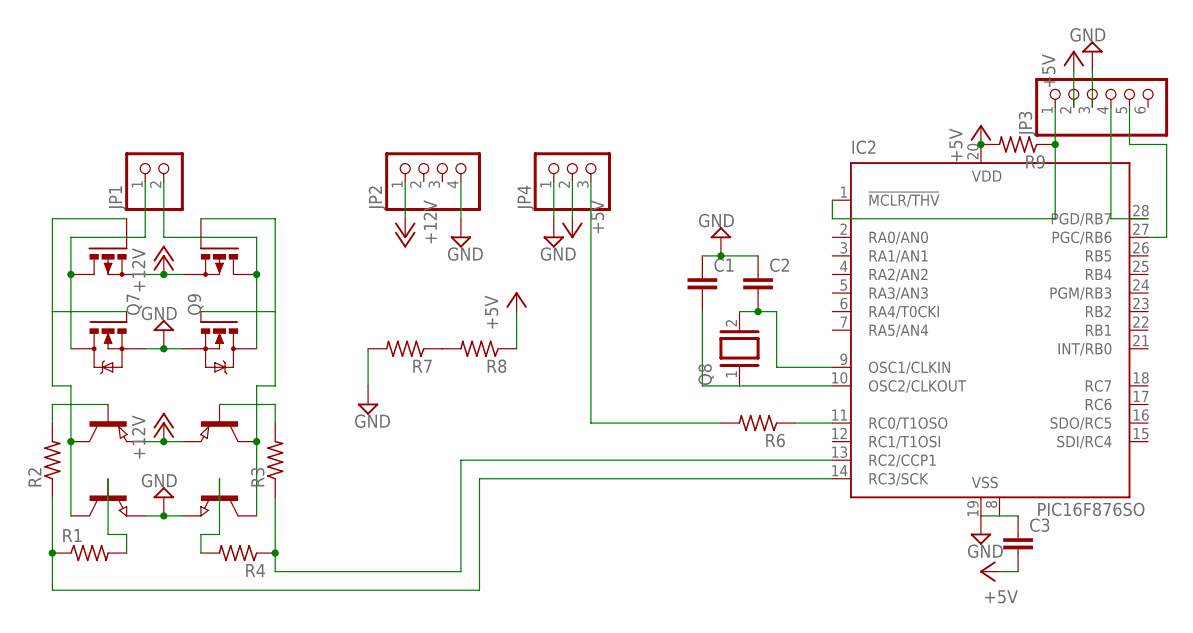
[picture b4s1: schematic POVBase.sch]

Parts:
C1, C2, C3: C-EUC0805; C0805
IC2: PIC16F876SO; SO28W
JP1: PINHD-1X2; 1X02
JP2: PINHD-1X4; 1X04
JP3: PINHD-1X6; 1X06
JP4: PINHD-1X3; 1X03
Q1, Q2: NPN-TRANSISTOR_SOT23; SOT23
Q3, Q4: PNP-TRANSISTOR_SOT23; SOT23
Q5, Q6: IRF540; TO220BV
Q7, Q9: PMOSFET_PTO220BV; TO220BV
Q8: XTAL/S; QS
R1, R2, R3, R4, R6, R7, R8, R9: R-US_R0805; R0805

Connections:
+5V: C3.2, IC2.20 (VDD), JP3.2, JP4.2, R8.1, R9.2
+12V: JP2.1, Q3.2 (E), Q4.2 (E), Q7.S, Q9.S
GND: C1.1, C2.1, C3.1, IC2.8 (VSS), IC2.19 (VSS), JP2.4, JP3.3, JP4.1, Q1.2 (E), Q2.2 (E), Q5.S, Q6.S, R7.2
unnamed: Q1.3 (C), Q3.3 (C), Q5.G, Q7.G
unnamed: Q1.1 (B), R1.2
unnamed: Q2.1 (B), R4.2
unnamed: Q2.3 (C), Q4.3 (C), Q6.G, Q9.G
unnamed: Q3.1 (B), R2.2
unnamed: Q4.1 (B), R3.2
unnamed: IC2.14 (RC3/SCK), R1.1, R2.1
unnamed: IC2.13 (RC2/CCP1), R3.1, R4.1
unnamed: JP4.3, R6.2
unnamed: JP1.2, Q6.D, Q9.D
unnamed: JP1.1, Q5.D, Q7.D
unnamed: IC2.1 (!MCLR/THV), JP3.1, R9.1
unnamed: IC2.28 (PGD/RB7), JP3.4
unnamed: IC2.27 (PGC/RB6), JP3.5
unnamed: IC2.11 (RC0/T1OSO), R6.1
unnamed: C1.2, IC2.10 (OSC2/CLKOUT), Q8.1
unnamed: C2.2, IC2.9 (OSC1/CLKIN), Q8.2
unnamed: R7.1, R8.2

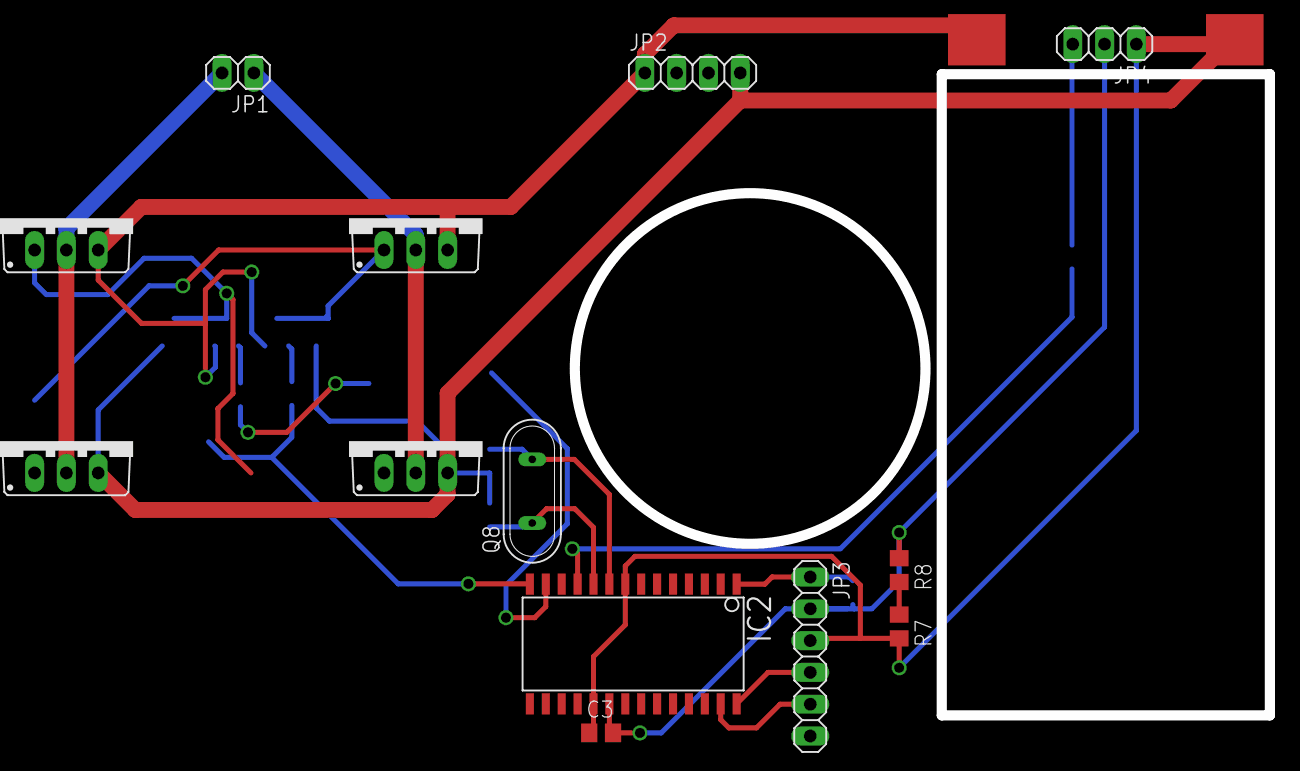
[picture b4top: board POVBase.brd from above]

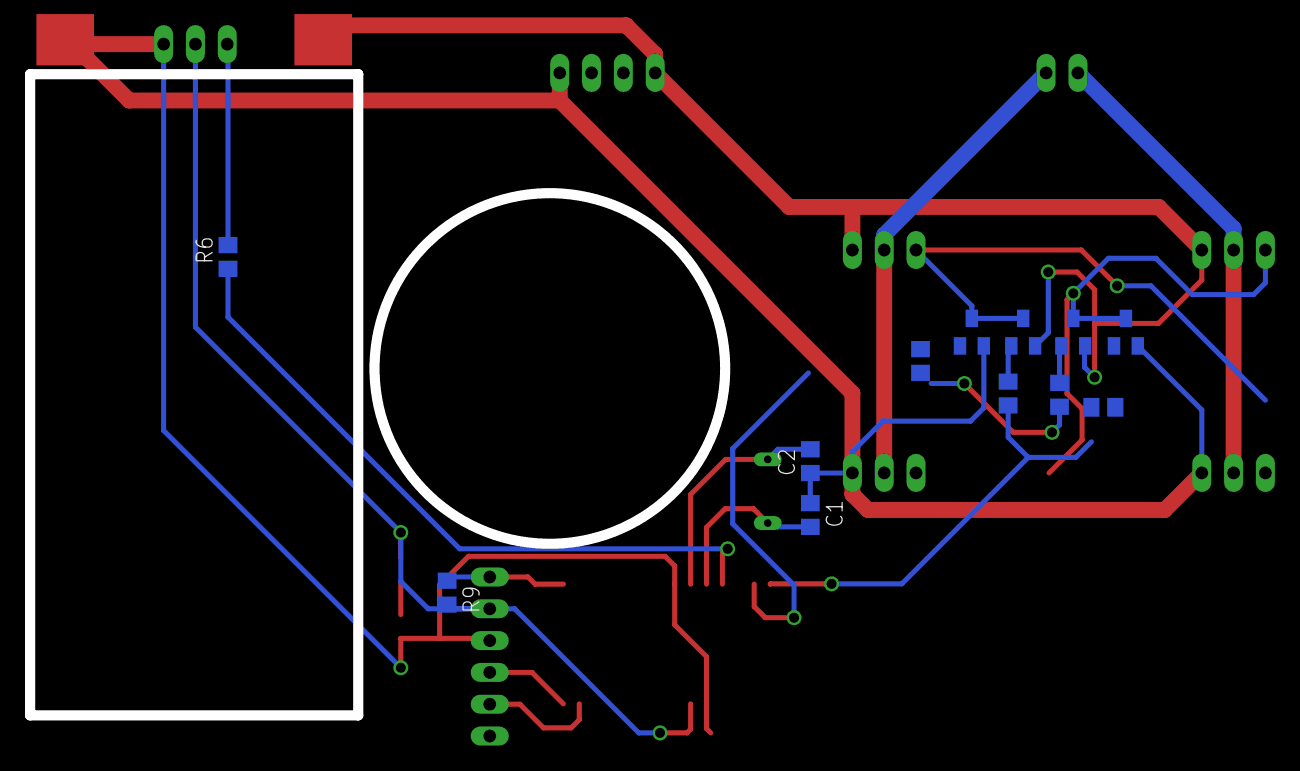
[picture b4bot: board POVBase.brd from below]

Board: 2 copper layers, 25 parts (12 on the bottom side), 21 nets.

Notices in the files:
parts and their libraries:
SparkFun-Coils: Licensing: Creative Commons ShareAlike 4.0 International - https://creativecommons.org/licenses/by-sa/4.0
